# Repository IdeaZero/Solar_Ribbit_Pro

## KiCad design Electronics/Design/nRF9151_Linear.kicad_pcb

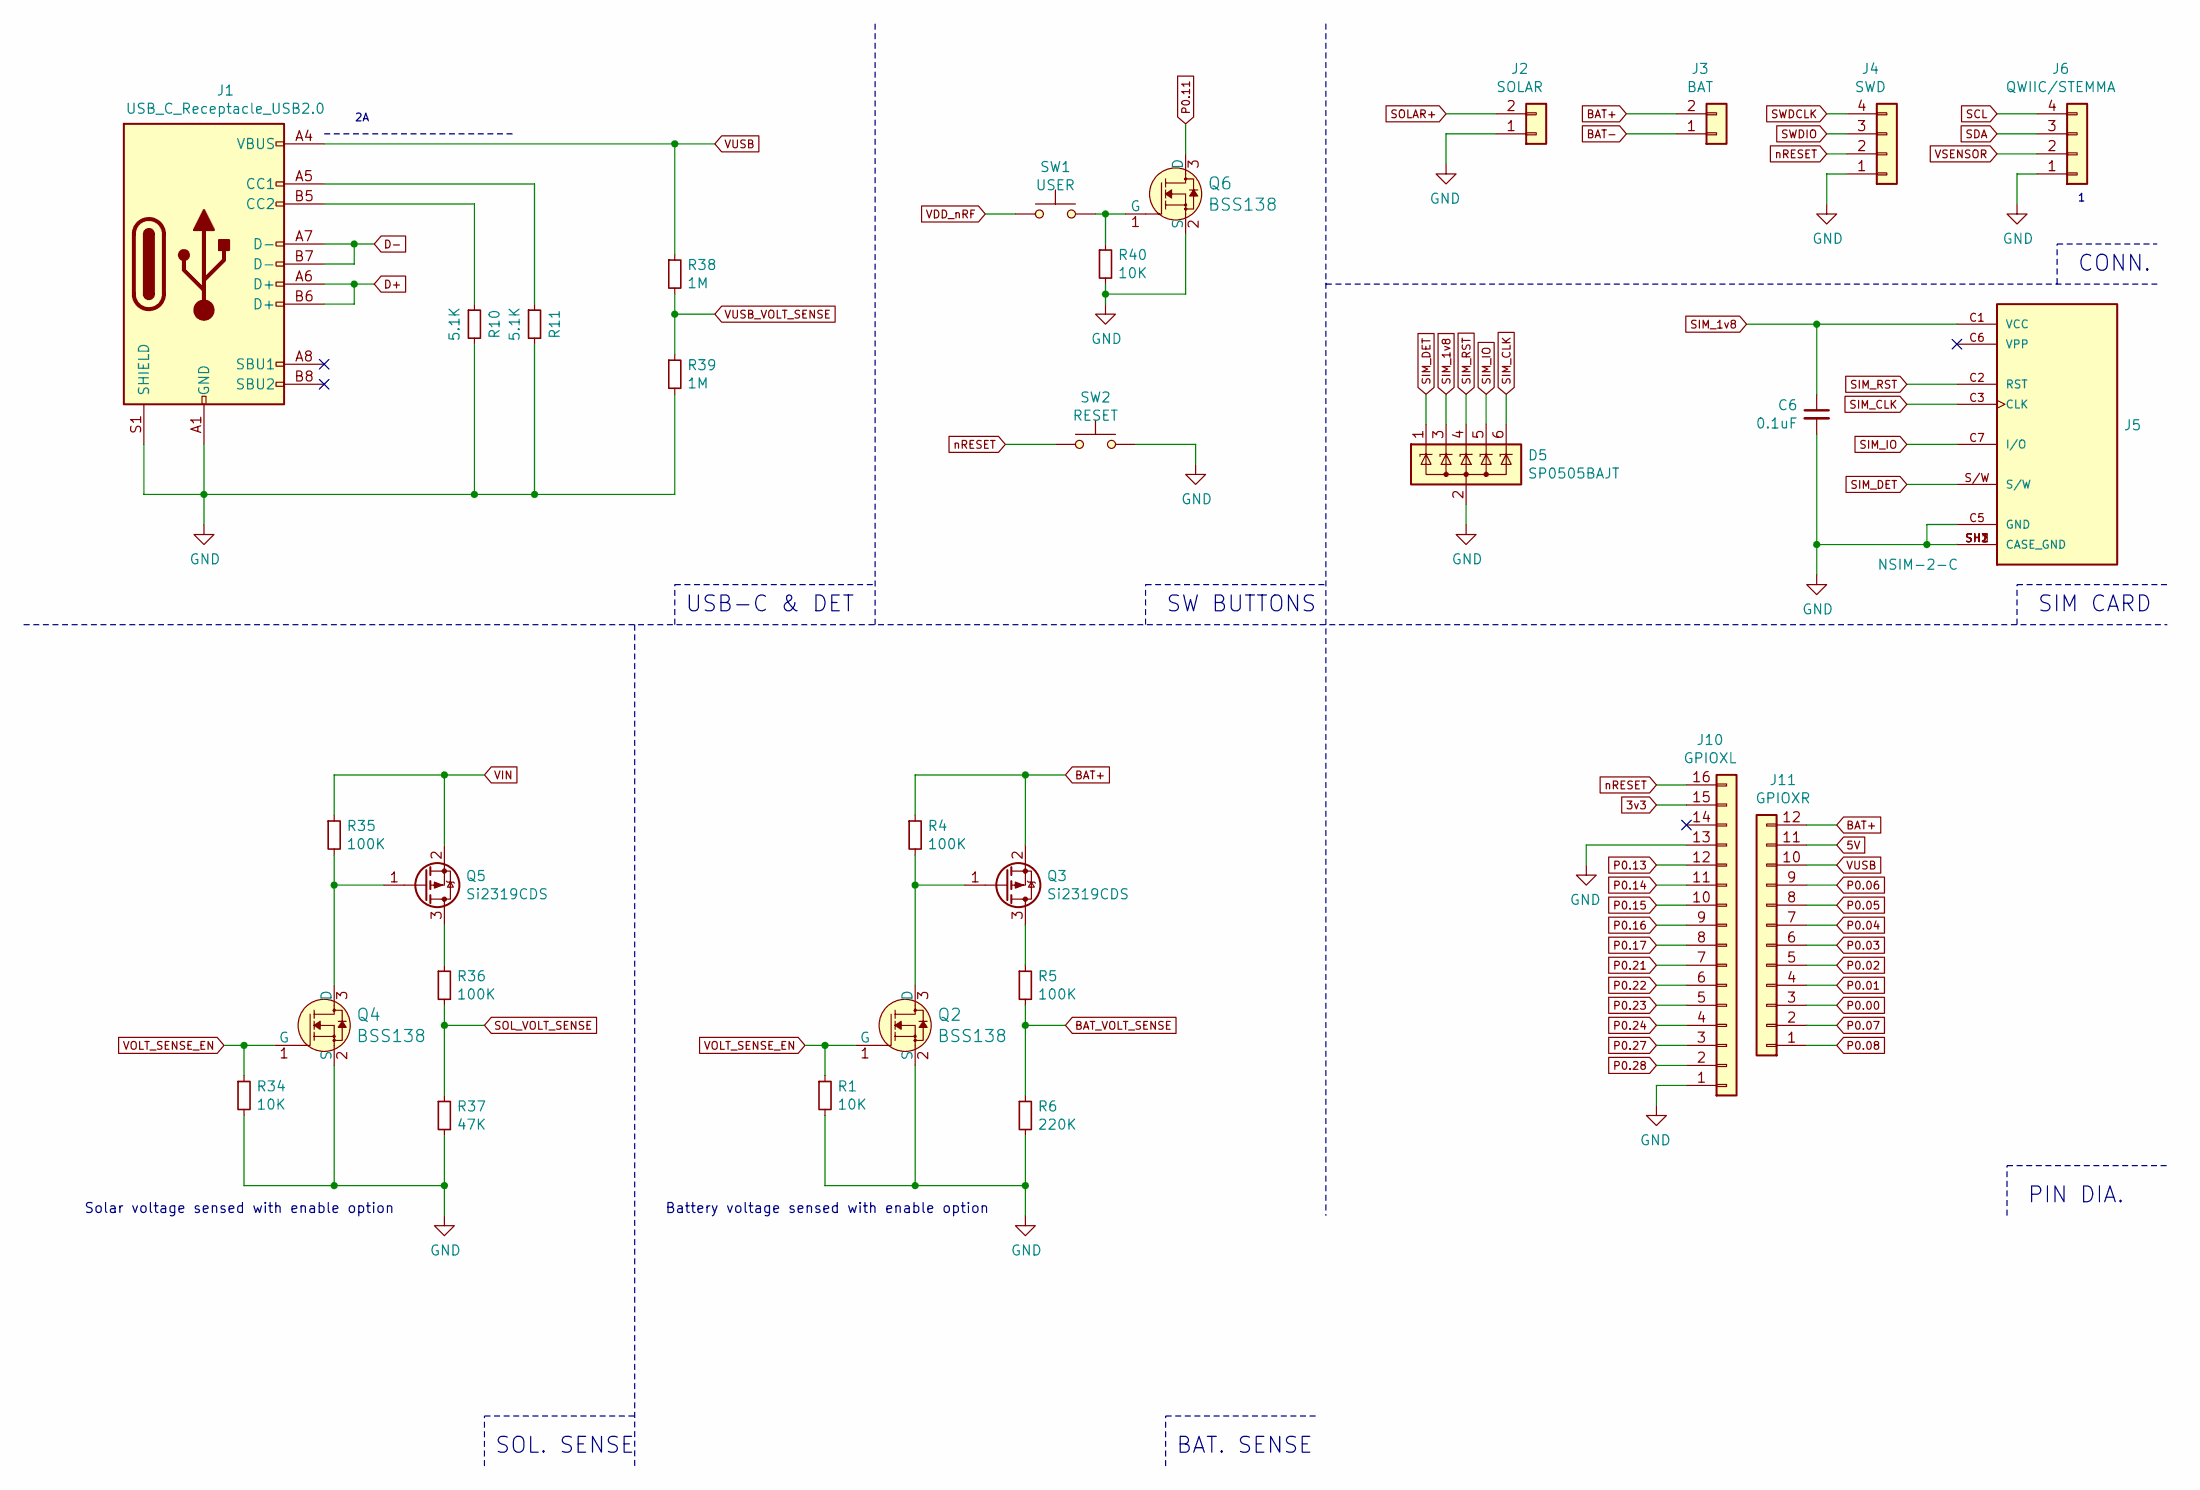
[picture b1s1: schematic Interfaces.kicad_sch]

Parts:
C6: 0.1uF; C_0402_1005Metric
D5: SP0505BAJT; SOT-363_SC-70-6
J1: USB_C_Receptacle_USB2.0; USB_TYPE-C-31-M-12_ExtraPad
J2: SOLAR; JST_PH_B2B-PH-SM4-TB_1x02-1MP_P2.00mm_Vertical
J3: BAT; JST_PH_B2B-PH-SM4-TB_1x02-1MP_P2.00mm_Vertical
J4: SWD; PinHeader_1x04_P2.54mm_Vertical
J5: NSIM-2-C; PARTREV 1.0
J6: QWIIC/STEMMA; JST_SH_SM04B-SRSS-TB_1x04-1MP_P1.00mm_Horizontal
J10: GPIOXL; PinHeader_1x16_P2.54mm_Vertical
J11: GPIOXR; PinHeader_1x12_P2.54mm_Vertical
Q2, Q4, Q6: BSS138; SOT-23; MPN BSS138; Digi-Key_PN BSS138CT-ND
Q3, Q5: Si2319CDS; SOT-23
R1, R34, R40: 10K; R_0402_1005Metric
R4, R5, R35, R36: 100K; R_0402_1005Metric
R6: 220K; R_0402_1005Metric
R10, R11: 5.1K; R_0402_1005Metric
R37: 47K; R_0402_1005Metric
R38, R39: 1M; R_0402_1005Metric
SW1: USER; SPST_PTS815XX
SW2: RESET; SPST_PTS815XX

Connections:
3v3: J10.15; also elsewhere on the board
5V: J11.11; also elsewhere on the board
BAT+: J3.2, J11.12, Q3.2 (S), R4.1; also elsewhere on the board
BAT-: J3.1; also elsewhere on the board
BAT_VOLT_SENSE: R5.2, R6.1; also elsewhere on the board
D+: J1.A6 (D+), J1.B6 (D+); also elsewhere on the board
D-: J1.A7 (D-), J1.B7 (D-); also elsewhere on the board
GND: C6.2, D5.2 (A), J1.A1 (GND), J1.A12 (GND), J1.B1 (GND), J1.B12 (GND), J1.S1 (SHIELD), J2.1, J4.1, J5.C5 (GND), J5.SH1 (CASE_GND), J5.SH2 (CASE_GND), J5.SH3 (CASE_GND), J6.1, J10.1, J10.13, Q2.2 (S), Q4.2 (S), Q6.2 (S), R1.2, R6.2, R10.2, R11.2, R34.2, R37.2, R39.2, R40.2, SW2.3, SW2.4; also elsewhere on the board
unnamed: J1.A5 (CC1), R11.1
unnamed: J1.B5 (CC2), R10.1
unnamed: Q2.3 (D), Q3.1 (G), R4.2
unnamed: Q3.3 (D), R5.1
unnamed: Q4.3 (D), Q5.1 (G), R35.2
unnamed: Q5.3 (D), R36.1
unnamed: Q6.1 (G), R40.1, SW1.3, SW1.4
P0.00: J11.3; also elsewhere on the board
P0.01: J11.4; also elsewhere on the board
P0.02: J11.5; also elsewhere on the board
P0.03: J11.6; also elsewhere on the board
P0.04: J11.7; also elsewhere on the board
P0.05: J11.8; also elsewhere on the board
P0.06: J11.9; also elsewhere on the board
P0.07: J6.4, J11.2; also elsewhere on the board
P0.08: J6.3, J11.1; also elsewhere on the board
P0.11: Q6.3 (D); also elsewhere on the board
P0.12: Q2.1 (G), Q4.1 (G), R1.1, R34.1; also elsewhere on the board
P0.13: J10.12; also elsewhere on the board
P0.14: J10.11; also elsewhere on the board
P0.15: J10.10; also elsewhere on the board
P0.16: J10.9; also elsewhere on the board
P0.17: J10.8; also elsewhere on the board
P0.19: R36.2, R37.1; also elsewhere on the board
P0.20: R38.2, R39.1; also elsewhere on the board
P0.21: J10.7; also elsewhere on the board
P0.22: J10.6; also elsewhere on the board
P0.23: J10.5; also elsewhere on the board
P0.24: J10.4; also elsewhere on the board
P0.27: J10.3; also elsewhere on the board
P0.28: J10.2; also elsewhere on the board
SIM_1v8: C6.1, D5.3 (K), J5.C1 (VCC); also elsewhere on the board
SIM_CLK: D5.6 (K), J5.C3 (CLK); also elsewhere on the board
SIM_DET: D5.1 (K), J5.S/W; also elsewhere on the board
SIM_IO: D5.5 (K), J5.C7 (I/O); also elsewhere on the board
SIM_RST: D5.4 (K), J5.C2 (RST); also elsewhere on the board
SOLAR+: J2.2; also elsewhere on the board
SWDCLK: J4.4; also elsewhere on the board
SWDIO: J4.3; also elsewhere on the board
VDD_nRF: SW1.1, SW1.2; also elsewhere on the board
VIN: Q5.2 (S), R35.1; also elsewhere on the board
VSENSOR: J6.2; also elsewhere on the board
VUSB: J1.A4 (VBUS), J1.A9 (VBUS), J1.B4 (VBUS), J1.B9 (VBUS), J11.10, R38.1; also elsewhere on the board
nRESET: J4.2, J10.16, SW2.1, SW2.2; also elsewhere on the board

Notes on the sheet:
BAT. SENSE
CONN.
SIM CARD
PIN DIA.
Solar voltage sensed with enable option
USB-C & DET
SOL. SENSE
Battery voltage sensed with enable option
SW BUTTONS

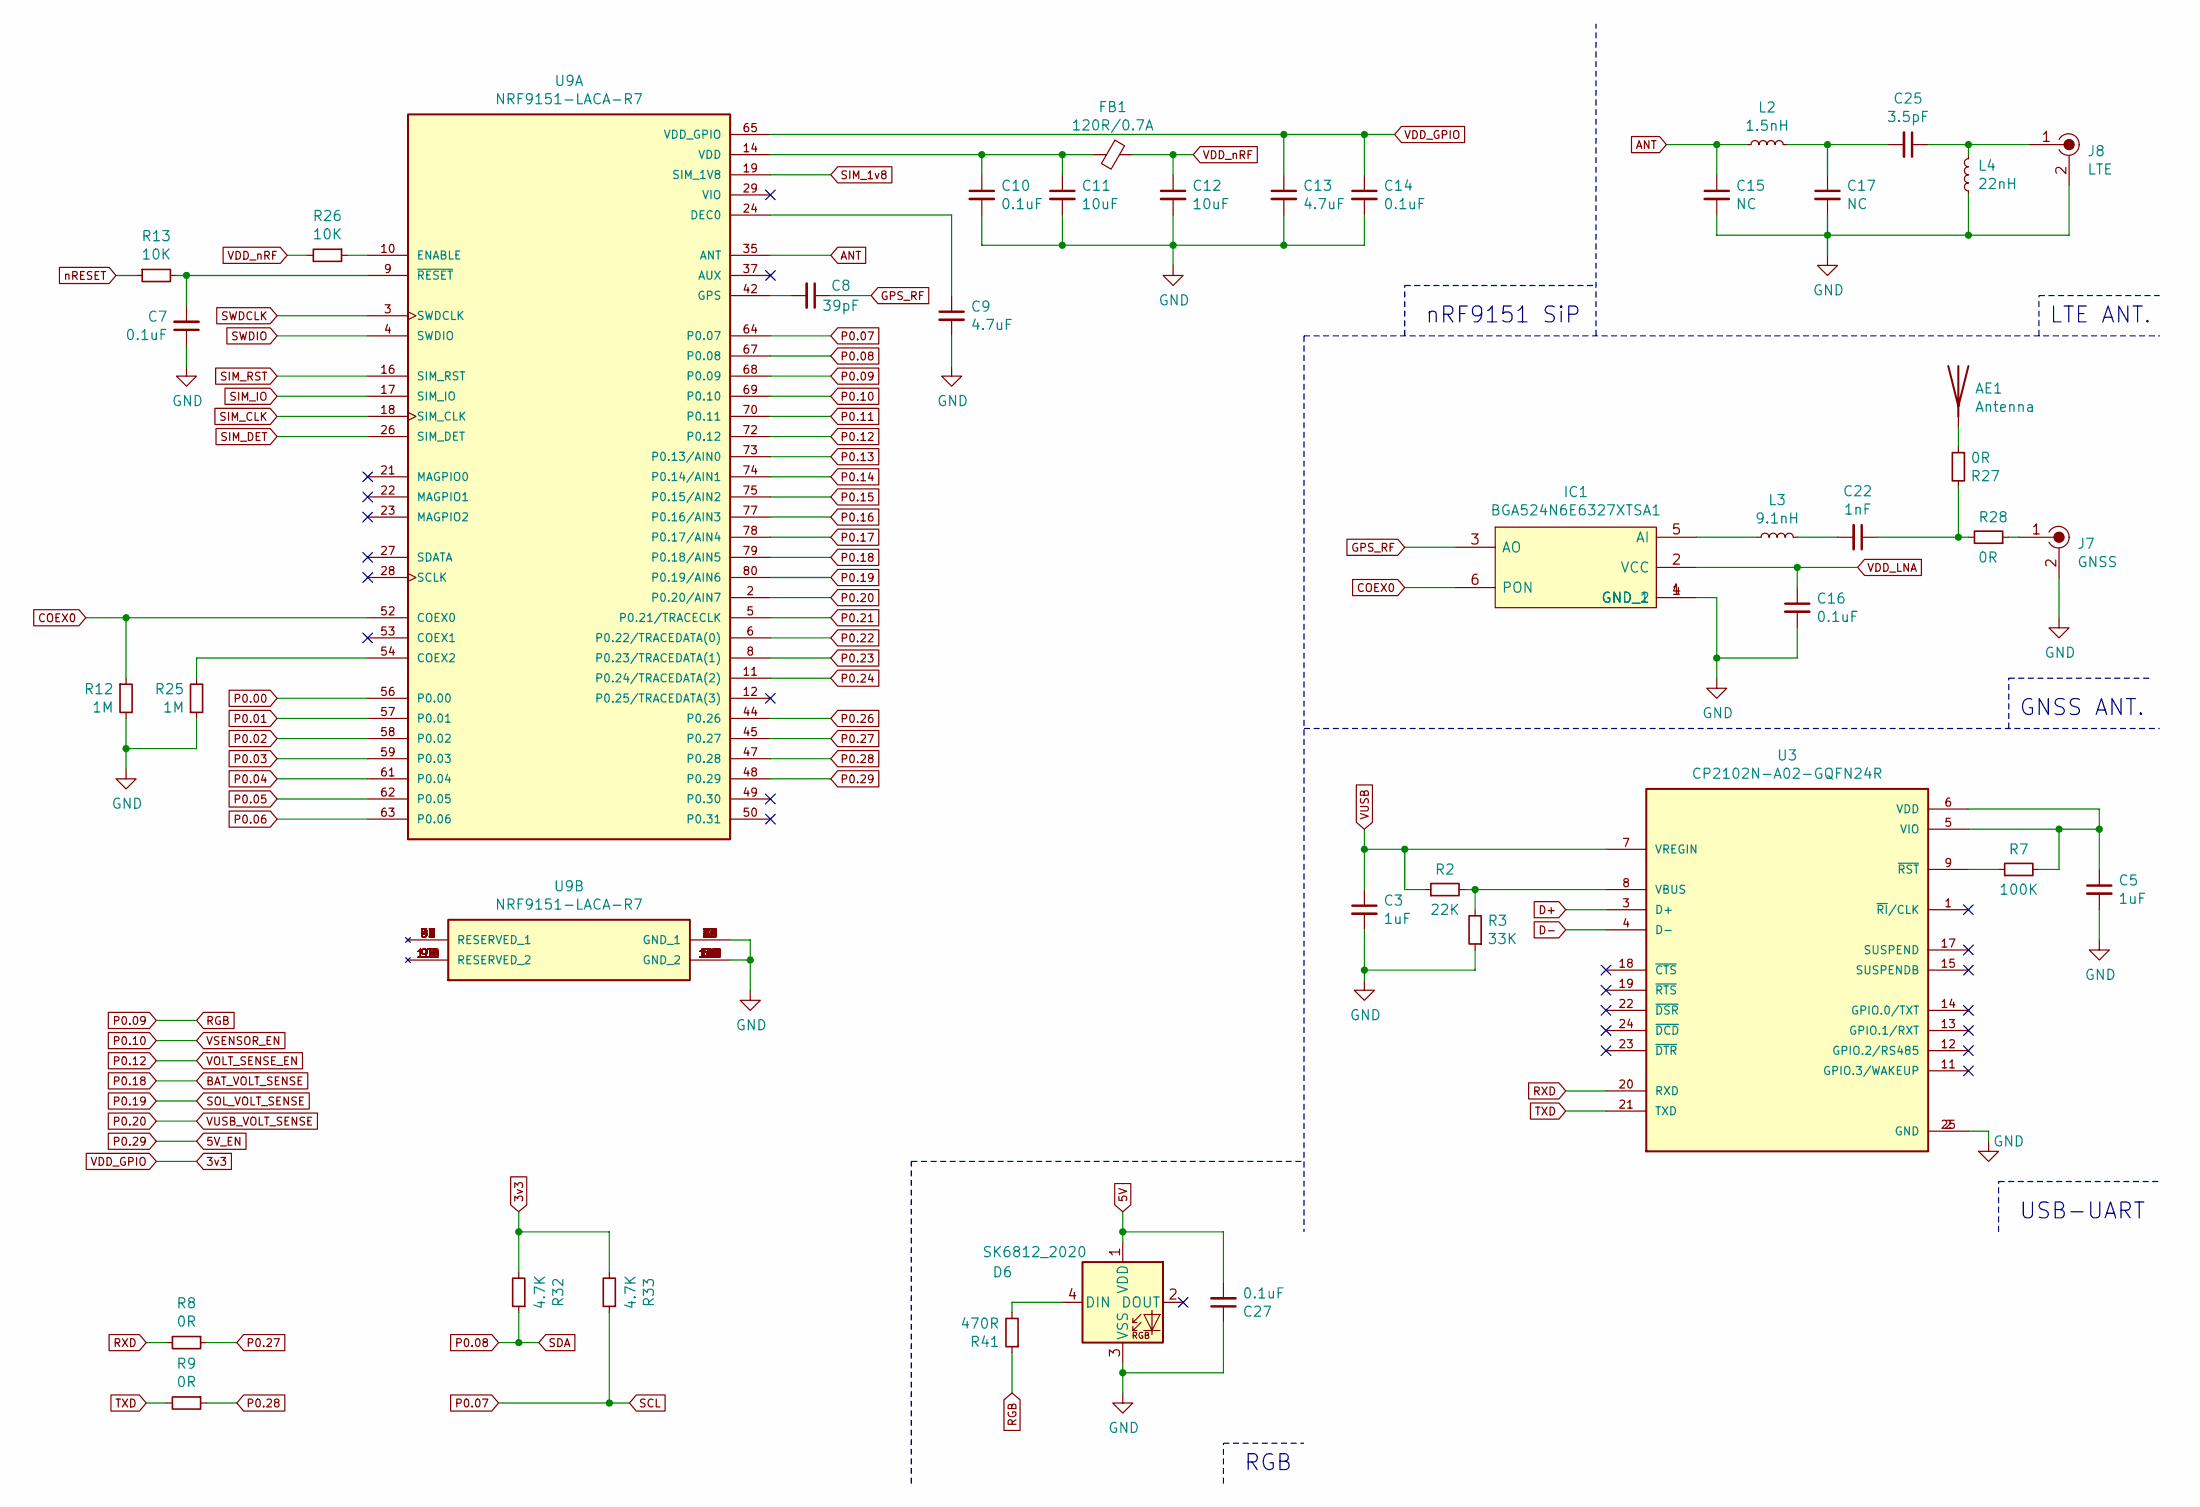
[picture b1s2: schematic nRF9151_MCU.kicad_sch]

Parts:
AE1: Antenna; YG0005AA
C3, C5: 1uF; C_0402_1005Metric
C7, C10, C14, C16, C27: 0.1uF; C_0402_1005Metric
C8: 39pF; C_0402_1005Metric
C9, C13: 4.7uF; C_0402_1005Metric
C11, C12: 10uF; C_0603_1608Metric
C15, C17: NC; C_0402_1005Metric
C22: 1nF; C_0402_1005Metric
C25: 3.5pF; C_0402_1005Metric
D6: SK6812_2020
FB1: 120R/0.7A; R_0603_1608Metric_Pad0.98x0.95mm_HandSolder
IC1: BGA524N6E6327XTSA1; Manufacturer_Part_Number BGA524N6E6327XTSA1; Mouser Part Number 726-A524N6E6327XTSA1
J7: GNSS; U.FL-R-SMT-1; MPN U.FL-R-SMT(10); Digi-Key_PN H9161CT-ND
J8: LTE; U.FL-R-SMT-1; MPN U.FL-R-SMT(10); Digi-Key_PN H9161CT-ND
L2: 1.5nH; L_0402_1005Metric
L3: 9.1nH; L_0402_1005Metric
L4: 22nH; L_0402_1005Metric
R2: 22K; R_0402_1005Metric
R3: 33K; R_0402_1005Metric
R7: 100K; R_0402_1005Metric
R8, R9, R27, R28: 0R; R_0402_1005Metric
R12, R25: 1M; R_0402_1005Metric
R13, R26: 10K; R_0402_1005Metric
R32, R33: 4.7K; R_0402_1005Metric
R41: 470R; R_0402_1005Metric
U3: CP2102N-A02-GQFN24R; PARTREV 1.3
U9: NRF9151-LACA-R7; PARTREV 1.0

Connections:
3v3: C13.1, C14.1, R32.2, R33.2, U9.65 (VDD_GPIO); also elsewhere on the board
5V: C27.2, D6.1 (VDD); also elsewhere on the board
5V_EN: U9.48 (P0.29); also elsewhere on the board
ANT: C15.1, L2.1, U9.35 (ANT)
BAT_VOLT_SENSE: U9.79 (P0.18/AIN5); also elsewhere on the board
COEX0: IC1.6 (PON), R12.1, U9.52 (COEX0)
D+: U3.3 (D+); also elsewhere on the board
D-: U3.4 (D-); also elsewhere on the board
GND: C3.2, C5.2, C7.1, C9.2, C10.2, C11.2, C12.2, C13.2, C14.2, C15.2, C16.2, C17.2, C27.1, D6.3 (VSS), IC1.1 (GND_1), IC1.4 (GND_2), J7.2, J8.2, L4.1, R3.1, R12.2, R25.1, U3.2 (GND), U3.25 (GND), U9.1 (GND_1), U9.7 (GND_1), U9.13 (GND_1), U9.15 (GND_1), U9.20 (GND_1), U9.25 (GND_1), U9.30 (GND_1), U9.34 (GND_1), U9.36 (GND_1), U9.38 (GND_1), U9.39 (GND_1), U9.40 (GND_1), U9.41 (GND_1), U9.43 (GND_1), U9.46 (GND_1), U9.51 (GND_2), U9.55 (GND_2), U9.60 (GND_2), U9.66 (GND_2), U9.71 (GND_2), U9.76 (GND_2), U9.105 (GND_2), U9.106 (GND_2), U9.107 (GND_2), U9.108 (GND_2), U9.109 (GND_2), U9.110 (GND_2), U9.111 (GND_2), U9.112 (GND_2), U9.113 (GND_2); also elsewhere on the board
GPS_RF: C8.1, IC1.3 (AO)
unnamed: AE1.1 (A), R27.1
unnamed: C17.1, C25.2, L2.2
unnamed: C22.1, R27.2, R28.2
unnamed: C22.2, L3.2
unnamed: C25.1, J8.1, L4.2
unnamed: D6.4 (DIN), R41.2
unnamed: IC1.5 (AI), L3.1
unnamed: J7.1, R28.1
unnamed: R2.2, R3.2, U3.8 (VBUS)
unnamed: C5.1, R7.2, U3.5 (VIO), U3.6 (VDD)
unnamed: R7.1, U3.9 (~RST)
unnamed: R25.2, U9.54 (COEX2)
unnamed: C9.1, U9.24 (DEC0)
unnamed: R26.1, U9.10 (ENABLE)
unnamed: C8.2, U9.42 (GPS)
unnamed: C10.1, C11.1, FB1.2, U9.14 (VDD)
unnamed: C7.2, R13.2, U9.9 (~RESET)
P0.00: U9.56 (P0.00); also elsewhere on the board
P0.01: U9.57 (P0.01); also elsewhere on the board
P0.02: U9.58 (P0.02); also elsewhere on the board
P0.03: U9.59 (P0.03); also elsewhere on the board
P0.04: U9.61 (P0.04); also elsewhere on the board
P0.05: U9.62 (P0.05); also elsewhere on the board
P0.06: U9.63 (P0.06); also elsewhere on the board
P0.07: R33.1, U9.64 (P0.07); also elsewhere on the board
P0.08: R32.1, U9.67 (P0.08); also elsewhere on the board
P0.09: R41.1, U9.68 (P0.09)
P0.10: U9.69 (P0.10); also elsewhere on the board
P0.11: U9.70 (P0.11); also elsewhere on the board
P0.12: U9.72 (P0.12); also elsewhere on the board
P0.13: U9.73 (P0.13/AIN0); also elsewhere on the board
P0.14: U9.74 (P0.14/AIN1); also elsewhere on the board
P0.15: U9.75 (P0.15/AIN2); also elsewhere on the board
P0.16: U9.77 (P0.16/AIN3); also elsewhere on the board
P0.17: U9.78 (P0.17/AIN4); also elsewhere on the board
P0.19: U9.80 (P0.19/AIN6); also elsewhere on the board
P0.20: U9.2 (P0.20/AIN7); also elsewhere on the board
P0.21: U9.5 (P0.21/TRACECLK); also elsewhere on the board
P0.22: U9.6 (P0.22/TRACEDATA(0)); also elsewhere on the board
P0.23: U9.8 (P0.23/TRACEDATA(1)); also elsewhere on the board
P0.24: U9.11 (P0.24/TRACEDATA(2)); also elsewhere on the board
P0.26: U9.44 (P0.26)
P0.27: R8.1, U9.45 (P0.27); also elsewhere on the board
P0.28: R9.1, U9.47 (P0.28); also elsewhere on the board
RXD: R8.2, U3.20 (RXD)
SIM_1v8: U9.19 (SIM_1V8); also elsewhere on the board
SIM_CLK: U9.18 (SIM_CLK); also elsewhere on the board
SIM_DET: U9.26 (SIM_DET); also elsewhere on the board
SIM_IO: U9.17 (SIM_IO); also elsewhere on the board
SIM_RST: U9.16 (SIM_RST); also elsewhere on the board
SWDCLK: U9.3 (SWDCLK); also elsewhere on the board
SWDIO: U9.4 (SWDIO); also elsewhere on the board
TXD: R9.2, U3.21 (TXD)
VDD_LNA: C16.1, IC1.2 (VCC); also elsewhere on the board
VDD_nRF: C12.1, FB1.1, R26.2; also elsewhere on the board
VUSB: C3.1, R2.1, U3.7 (VREGIN); also elsewhere on the board
nRESET: R13.1; also elsewhere on the board

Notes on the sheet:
nRF9151 SiP
GNSS ANT.
RGB
USB-UART
LTE ANT.

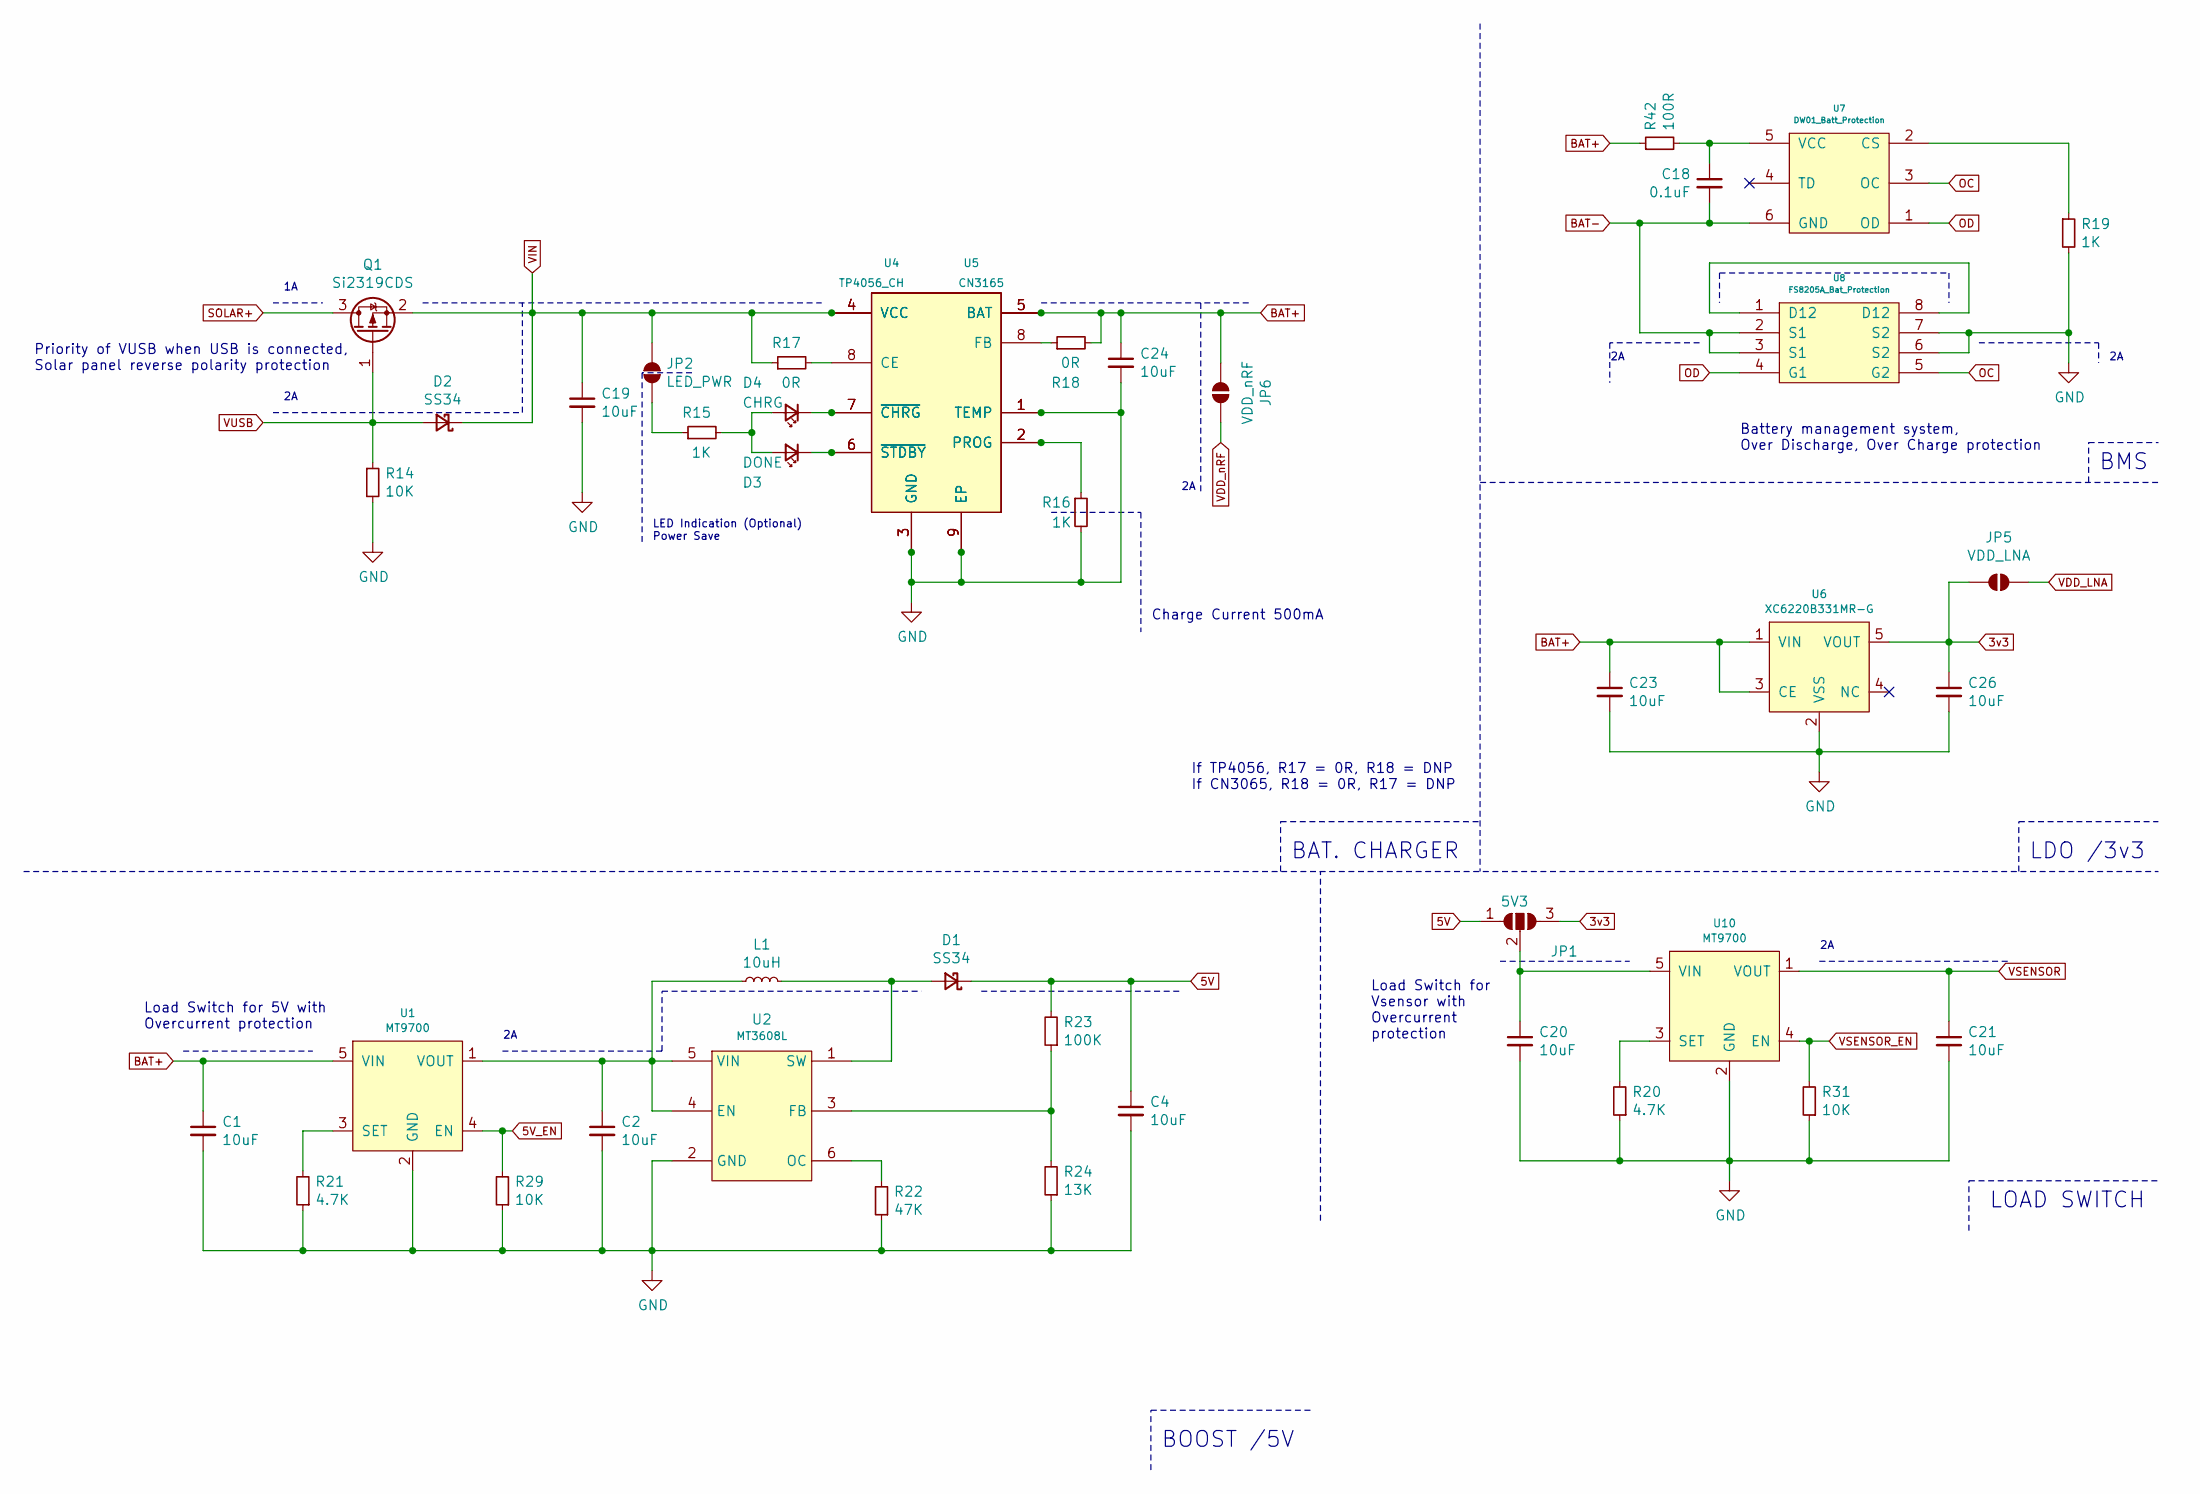
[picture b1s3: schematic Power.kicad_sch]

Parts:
C1, C2, C4, C19, C20, C21, C23, C24, C26: 10uF; C_0603_1608Metric
C18: 0.1uF; C_0402_1005Metric
D1, D2: SS34; D_SOD-123F
D3: DONE; LED_0603_1608Metric
D4: CHRG; LED_0603_1608Metric
JP1: 5V3; SolderJumper-3_P1.3mm_Open_RoundedPad1.0x1.5mm
JP2: LED_PWR; SolderJumper-2_P1.3mm_Open_RoundedPad1.0x1.5mm
JP5: VDD_LNA; SolderJumper-2_P1.3mm_Open_RoundedPad1.0x1.5mm
JP6: VDD_nRF; SolderJumper-2_P1.3mm_Open_RoundedPad1.0x1.5mm
L1: 10uH; Inductor_GPSR0520_HCM1A4020V2_1R0
Q1: Si2319CDS; SOT-23
R14, R29, R31: 10K; R_0402_1005Metric
R15, R16, R19: 1K; R_0402_1005Metric
R17, R18: 0R; R_0402_1005Metric
R20, R21: 4.7K; R_0402_1005Metric
R22: 47K; R_0402_1005Metric
R23: 100K; R_0402_1005Metric
R24: 13K; R_0402_1005Metric
R42: 100R; R_0402_1005Metric
U1, U10: MT9700; SOT-23-5
U2: MT3608L; SOT-23-6
U4: TP4056_CH; SOP-8
U5: CN3165; DFN-8-1EP_3x3mm_P0.5mm_EP1.66x2.38mm
U6: XC6220B331MR-G; SOT-23-5
U7: DW01_Batt_Protection; SOT-23-6
U8: FS8205A_Bat_Protection; TSSOP-8_4.4x3mm_P0.65mm

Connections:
3v3: C26.1, JP1.3 (B), JP5.1 (A), U6.5 (VOUT); also elsewhere on the board
5V: C4.1, D1.1 (K), JP1.1 (A), R23.2; also elsewhere on the board
5V_EN: R29.2, U1.4 (EN); also elsewhere on the board
BAT+: C1.1, C23.1, C24.1, JP6.2 (B), R18.2, R42.1, U1.5 (VIN), U4.5 (BAT), U5.5 (BAT), U6.1 (VIN), U6.3 (CE); also elsewhere on the board
BAT-: C18.2, U7.6 (GND), U8.2 (S1), U8.3 (S1); also elsewhere on the board
GND: C1.2, C2.2, C4.2, C19.2, C20.2, C21.2, C23.2, C24.2, C26.2, R14.2, R16.2, R19.2, R20.1, R21.1, R22.1, R24.1, R29.1, R31.1, U1.2 (GND), U2.2 (GND), U4.1 (TEMP), U4.3 (GND), U4.9 (EP), U5.1 (TEMP), U5.3 (GND), U5.9 (EP), U6.2 (VSS), U8.6 (S2), U8.7 (S2), U10.2 (GND); also elsewhere on the board
unnamed: D1.2 (A), L1.2, U2.1 (SW)
unnamed: D3.2 (A), D4.2 (A), R15.2
unnamed: D3.1 (K), U4.6 (~STDBY), U5.6 (~STDBY)
unnamed: D4.1 (K), U4.7 (~CHRG), U5.7 (~CHRG)
unnamed: C20.1, JP1.2 (C), U10.5 (VIN)
unnamed: JP2.2 (B), R15.1
unnamed: R21.2, U1.3 (SET)
unnamed: C2.1, L1.1, U1.1 (VOUT), U2.4 (EN), U2.5 (VIN)
unnamed: R23.1, R24.2, U2.3 (FB)
unnamed: R22.2, U2.6 (OC)
unnamed: R17.2, U4.8 (CE)
unnamed: R16.1, U4.2 (PROG), U5.2 (PROG)
unnamed: R18.1, U5.8 (FB)
unnamed: R19.1, U7.2 (CS)
unnamed: C18.1, R42.2, U7.5 (VCC)
unnamed: U8.1 (D12), U8.8 (D12)
unnamed: R20.2, U10.3 (SET)
OC: U7.3 (OC), U8.5 (G2)
OD: U7.1 (OD), U8.4 (G1)
P0.10: R31.2, U10.4 (EN); also elsewhere on the board
SOLAR+: Q1.3 (D); also elsewhere on the board
VDD_LNA: JP5.2 (B); also elsewhere on the board
VDD_nRF: JP6.1 (A); also elsewhere on the board
VIN: C19.1, D2.1 (K), JP2.1 (A), Q1.2 (S), R17.1, U4.4 (VCC), U5.4 (VCC); also elsewhere on the board
VSENSOR: C21.1, U10.1 (VOUT); also elsewhere on the board
VUSB: D2.2 (A), Q1.1 (G), R14.1; also elsewhere on the board

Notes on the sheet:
Charge Current 500mA
Load Switch for 5V with Overcurrent protection
LOAD SWITCH
BAT. CHARGER
If TP4056, R17 = 0R, R18 = DNP If CN3065, R18 = 0R, R17 = DNP
Priority of VUSB when USB is connected, Solar panel reverse polarity protection
BMS
LED Indication (Optional) Power Save
LDO /3v3
BOOST /5V
Load Switch for Vsensor with Overcurrent protection
Battery management system, Over Discharge, Over Charge protection

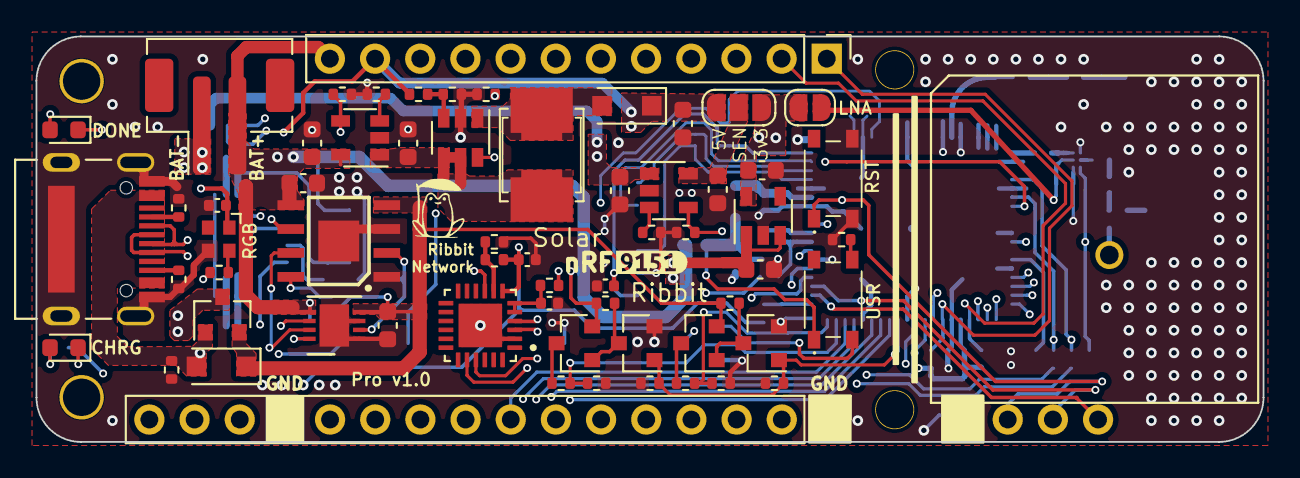
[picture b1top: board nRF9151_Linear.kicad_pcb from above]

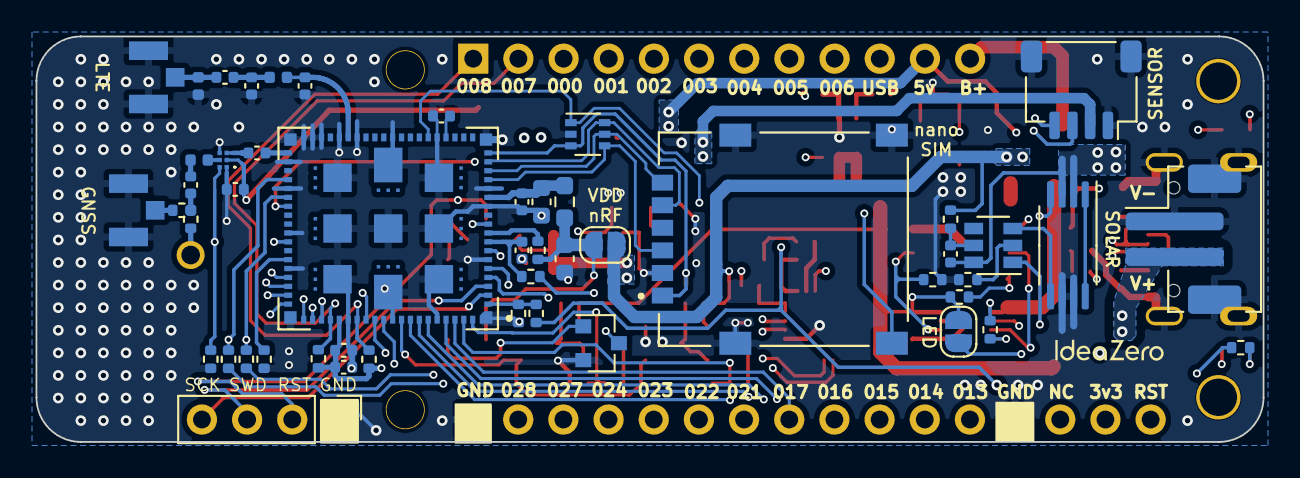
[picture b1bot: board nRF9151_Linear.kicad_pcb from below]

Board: 4 copper layers, 69.0 x 22.8 mm, 115 parts (51 on the bottom side), 97 nets.

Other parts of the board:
': '; IZ_logo_Small_2
kibuzzard-67CE8F77: G***; kibuzzard-67CE8F77

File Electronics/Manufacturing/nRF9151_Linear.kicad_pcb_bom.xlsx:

Designator | Quantity | Value | Footprint | MPN | DNP | Mount_Type | Comments
AE1 | 1 | Antenna | YG0005AA | YG0005AA |  | tht
C1, C11, C12, C19, C2, C20, C21, C23, C24, C26, C4 | 11 | 10uF | C_0603_1608Metric | CL10A106MO8NQNC |  | smt
C10, C14, C16, C18, C27, C6, C7 | 7 | 0.1uF | C_0402_1005Metric | CC0402KRX7R7BB104 |  | smt
C13, C9 | 2 | 4.7uF | C_0402_1005Metric | CL05A475MO5NUNC |  | smt
C15, C17 | 2 | NC | C_0402_1005Metric | - | YES | smt
C22 | 1 | 1nF | C_0402_1005Metric | CC0402KRX5R9BB102 |  | smt
C25 | 1 | 3.5pF | C_0402_1005Metric | GRM1555C1H3R5CA01D |  | smt
C3, C5 | 2 | 1uF | C_0402_1005Metric | CL05A105KO5NNNC |  | smt
C8 | 1 | 39pF | C_0402_1005Metric | CC0402JRNPO9BN390 |  | smt
D1, D2 | 2 | SS34 | D_SOD-123F | DSS34 |  | smt
D3 | 1 | DONE | LED_0603_1608Metric | PSC-1608U52GC-G4 |  | smt
D4 | 1 | CHRG | LED_0603_1608Metric | XL-1608SURC-06 |  | smt
D5 | 1 | ESD | SOT-363_SC-70-6 | PSC-1608U52GC-G4 |  | smt
D6 | 1 | RGB | SK6812_2020 | SK6812-EC20 |  | tht
FB1 | 1 | 120R/0.7A | R_0603_1608Metric | FCM1608KF-121T06 |  | smt
IC1 | 1 | BGA524N6E6327XTSA1 | BGA524N6E6327XTSA1 | BGA524N6E6327XTSA1 |  | smt
J1 | 1 | USC-C | USB_TYPE-C-31-M-12_ExtraPad | TYPE-C-31-M-12 |  | tht
J10 | 1 | GPIOXL | PinHeader_1x16_P2.54mm_Vertical | - | YES | tht
J11 | 1 | GPIOXR | PinHeader_1x12_P2.54mm_Vertical | - | YES | tht
J2 | 2 | SOLAR, BAT | JST_PH_B2B-PH-SM4-TB_1x02-1MP_P2.00mm_Vertical | PH-2PWB |  | smt
J4 | 1 | SWD | PinHeader_1x04_P2.54mm_Vertical | - | YES | tht
J5 | 1 | NSIM-2-C | NSIM-2-C | NSIM-2-C |  | smt
J6 | 1 | QWIIC/STEMMA | JST_SH_SM04B-SRSS-TB_1x04-1MP_P1.00mm_Horizontal | 1.0-4PWB |  | smt
J7 | 2 | GNSS, LTE | U.FL-R-SMT-1 | U.FL-R-SMT(10) |  | tht
JP1 | 1 | 5V3 | SolderJumper-3 | - | YES | tht
JP2 | 1 | LED_PWR | SolderJumper-2 | - | YES | tht
JP5 | 1 | VDD_LNA | SolderJumper-2 | - | YES | tht
JP6 | 1 | VDD_nRF | SolderJumper-2 | - | YES | tht
L1 | 1 | 10uH | 5x5 | GPSR0520-100M |  | tht
L2 | 1 | 1.5nH | L_0402_1005Metric | LQG15HS1N5S02D |  | smt
L3 | 1 | 9.1nH | L_0402_1005Metric | LQG15HS9N1J02D |  | smt
L4 | 1 | 22nH | L_0402_1005Metric | LQG15HS22NJ02D |  | smt
Q1, Q3, Q5 | 3 | Si2319CDS | SOT-23 | SI2319CDS |  | smt
Q2, Q4, Q6 | 3 | BSS138 | SOT-23 | BSS138 |  | smt
R1, R13, R14, R26, R29, R31, R34, R40 | 8 | 10K | R_0402_1005Metric | RC0402FR-0710KL |  | smt
R10, R11 | 2 | 5.1K | R_0402_1005Metric | RC0402FR-075K1L |  | smt
R12, R25, R38, R39 | 4 | 1M | R_0402_1005Metric | RC0402FR-071ML |  | smt
R15, R16, R19 | 3 | 1K | R_0402_1005Metric | RC0402FR-071KL |  | smt
R17, R18, R27, R28, R8, R9 | 6 | 0R | R_0402_1005Metric | RC0402JR-070RL |  | smt
R2 | 1 | 22K | R_0402_1005Metric | RC0402FR-0722KL |  | smt
R20, R21, R32, R33 | 4 | 4.7K | R_0402_1005Metric | RC0402FR-074K7L |  | smt
R22, R37 | 2 | 47K | R_0402_1005Metric | RC0402FR-0747KL |  | smt
R23, R35, R36, R4, R5, R7 | 6 | 100K | R_0402_1005Metric | RC0402FR-07100KL |  | smt
R24 | 1 | 13K | R_0402_1005Metric | RC0402FR-0713KL |  | smt
R3 | 1 | 33K | R_0402_1005Metric | RC0402FR-0733KL |  | smt
R41 | 1 | 470R | R_0402_1005Metric | RC0402FR-07470RL |  | smt
R42 | 1 | 100R | R_0402_1005Metric | RC0402FR-07100RL |  | smt
R6 | 1 | 220K | R_0402_1005Metric | RC0402FR-07220KL |  | smt
SW1 | 2 | USER, RESET | SPST_PTS815XX | PTS815SJK250SMTRLFS |  | smt
U1, U10 | 2 | MT9700 | SOT-23-5 | MT9700 |  | smt
U2 | 1 | MT3608L | SOT-23-6 | MT3608L |  | smt
U3 | 1 | CP2102N-A02-GQFN24R | CP2102N-A02-GQFN24R | CP2102N-A02 |  | smt | Optional -- for debugging
U4 | 1 | TP4056_CH | SOP-8 | TP4056 |  | smt
U5 | 1 | CN3165 | DFN-8-1EP_3x3mm_P0.5mm_EP1.66x2.38mm | CN3165 | YES | smt | Optional – Either this or TP4056 – anyone
U6 | 1 | XC6220B331MR-G | SOT-23-5 | XC6220B331MR-G |  | smt
U7 | 1 | DW01_Batt_Protection | SOT-23-6 | DW01 |  | smt
U8 | 1 | FS8205A_Bat_Protection | TSSOP-8_4.4x3mm_P0.65mm | FS8205A |  | smt
U9 | 1 | NRF9151-LACA-R7 | NRF9151-LACA-R7 | NRF9151-LACA-R7 |  | smt

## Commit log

2025-05-09 Getting started
2025-05-10 I2C Scan updated
2025-07-01 Firmware Code Update
